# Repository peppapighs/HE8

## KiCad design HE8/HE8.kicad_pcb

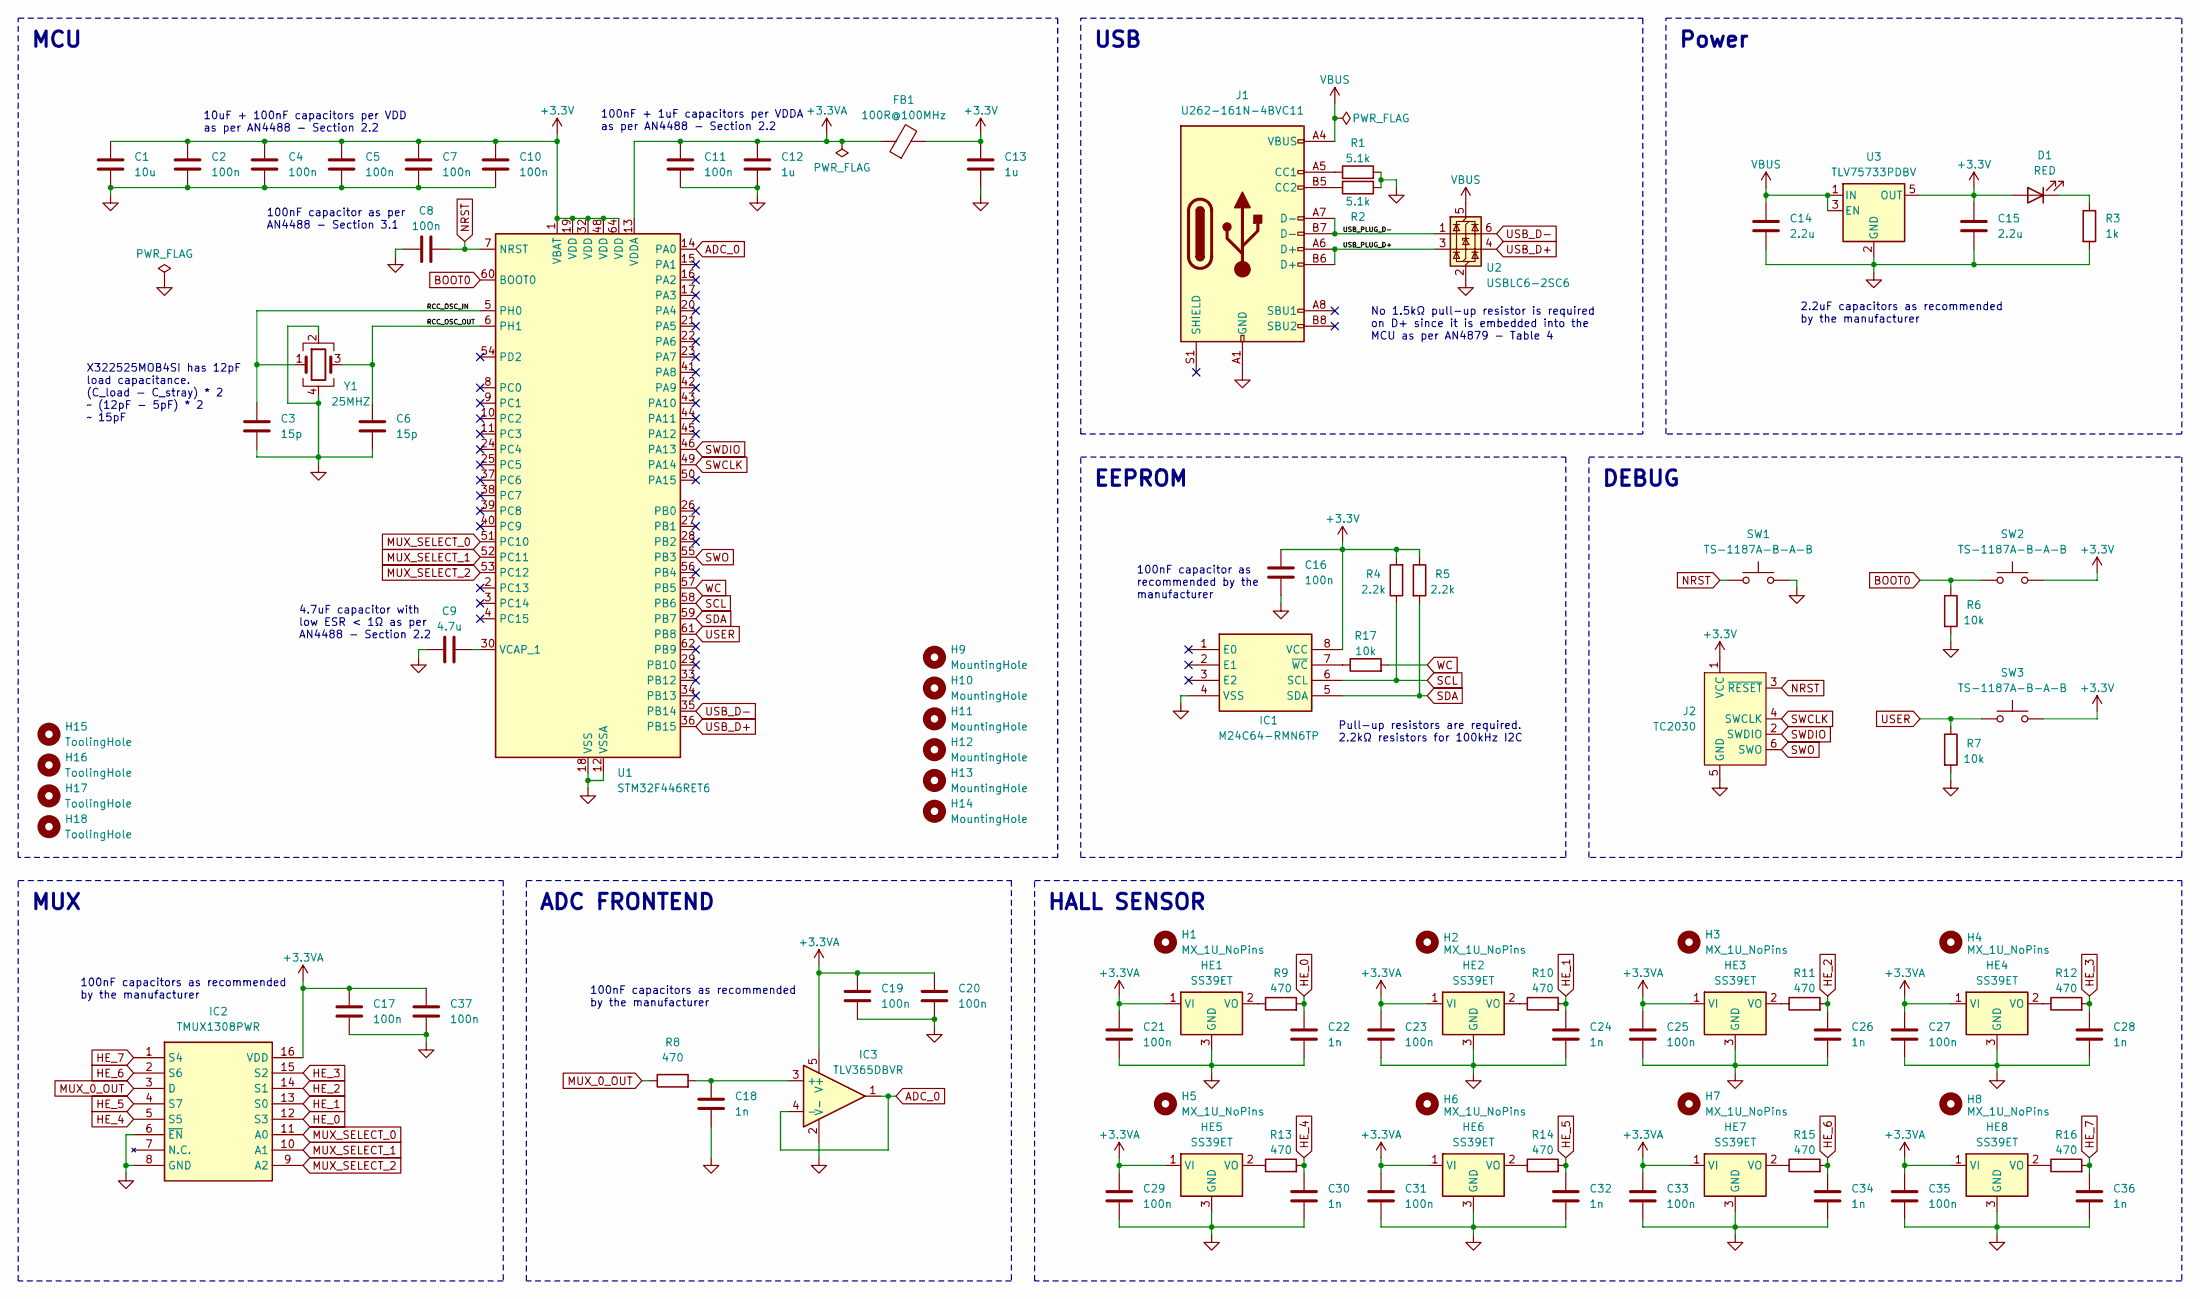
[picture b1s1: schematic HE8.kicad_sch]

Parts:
C1: 10u; C_0603_1608Metric
C2, C4, C5, C7, C8, C10, C11, C16, C17, C19, C20, C21, C23, C25, C27, C29, C31, C33, C35, C37: 100n; C_0402_1005Metric
C3, C6: 15p; C_0402_1005Metric
C9: 4.7u; C_0603_1608Metric
C12, C13: 1u; C_0603_1608Metric
C14, C15: 2.2u; C_0603_1608Metric
C18, C22, C24, C26, C28, C30, C32, C34, C36: 1n; C_0402_1005Metric
D1: RED; LED_0402_1005Metric
FB1: 100R@100MHz; L_0805_2012Metric
H1, H2, H3, H4, H5, H6, H7, H8: MX_1U_NoPins; MX-1U-NoPins
H9, H10, H11, H12, H13, H14: MountingHole; MountingHole_3.2mm_M3
H15, H16, H17, H18: ToolingHole
HE1, HE2, HE3, HE4, HE5, HE6, HE7, HE8: SS39ET; SOT95P280X140-3N; Mouser Part Number 785-SS39ET
IC1: M24C64-RMN6TP; SOIC127P600X175-8N; Mouser Part Number 511-M24C64-RMN6TP
IC2: TMUX1308PWR; SOP65P640X120-16N; Manufacturer_Part_Number TMUX1308PWR; Mouser Part Number 595-TMUX1308PWR
IC3: TLV365DBVR; SOT95P280X145-5N; Manufacturer_Part_Number TLV365DBVR
J1: U262-161N-4BVC11; USB_C_Receptacle_XKB_U262-16XN-4BVC11
J2: TC2030; Tag-Connect_TC2030-IDC-FP_2x03_P1.27mm_Vertical
R1, R2: 5.1k; R_0402_1005Metric
R3: 1k; R_0402_1005Metric
R4, R5: 2.2k; R_0402_1005Metric
R6, R7, R17: 10k; R_0402_1005Metric
R8, R9, R10, R11, R12, R13, R14, R15, R16: 470; R_0402_1005Metric
SW1, SW2, SW3: TS-1187A-B-A-B; SW_Push_1P1T_XKB_TS-1187A
U1: STM32F446RET6; LQFP-64_10x10mm_P0.5mm
U2: USBLC6-2SC6; SOT-23-6
U3: TLV75733PDBV; SOT-23-5
Y1: 25MHZ; Crystal_SMD_3225-4Pin_3.2x2.5mm

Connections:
+3.3V: C1.1, C2.1, C4.1, C5.1, C7.1, C10.1, C13.1, C15.1, C16.1, D1.2 (A), FB1.2, IC1.8 (VCC), J2.1 (VCC), R4.2, R5.1, SW2.2, SW3.2, U1.1 (VBAT), U1.19 (VDD), U1.32 (VDD), U1.48 (VDD), U1.64 (VDD), U3.5 (OUT)
+3.3VA: C11.1, C12.1, C17.1, C19.1, C20.1, C21.1, C23.1, C25.1, C27.1, C29.1, C31.1, C33.1, C35.1, C37.1, FB1.1, HE1.1 (VI), HE2.1 (VI), HE3.1 (VI), HE4.1 (VI), HE5.1 (VI), HE6.1 (VI), HE7.1 (VI), HE8.1 (VI), IC2.16 (VDD), IC3.5 (V+), U1.13 (VDDA)
/RCC_OSC_IN: C3.1, U1.5 (PH0), Y1.1
/RCC_OSC_OUT: C6.1, U1.6 (PH1), Y1.3
/USB_PLUG_D+: J1.A6 (D+), J1.B6 (D+), U2.3 (I/O2)
/USB_PLUG_D-: J1.A7 (D-), J1.B7 (D-), U2.1 (I/O1)
ADC_0: IC3.1, IC3.4 (-), U1.14 (PA0)
BOOT0: R6.1, SW2.1, U1.60 (BOOT0)
GND: C1.2, C2.2, C3.2, C4.2, C5.2, C6.2, C7.2, C8.1, C9.1, C10.2, C11.2, C12.2, C13.2, C14.2, C15.2, C16.2, C17.2, C18.2, C19.2, C20.2, C21.2, C22.2, C23.2, C24.2, C25.2, C26.2, C27.2, C28.2, C29.2, C30.2, C31.2, C32.2, C33.2, C34.2, C35.2, C36.2, C37.2, HE1.3 (GND), HE2.3 (GND), HE3.3 (GND), HE4.3 (GND), HE5.3 (GND), HE6.3 (GND), HE7.3 (GND), HE8.3 (GND), IC1.4 (VSS), IC2.6 (~EN), IC2.8 (GND), IC3.2 (V-), J1.A1 (GND), J1.A12 (GND), J1.B1 (GND), J1.B12 (GND), J2.5 (GND), R1.2, R2.1, R3.2, R6.2, R7.2, SW1.2, U1.12 (VSSA), U1.18 (VSS), U1.31 (VSS), U1.47 (VSS), U1.63 (VSS), U2.2 (GND), U3.2 (GND), Y1.2, Y1.4
HE_0: C22.1, IC2.12 (S3), R9.2
HE_1: C24.1, IC2.13 (S0), R10.2
HE_2: C26.1, IC2.14 (S1), R11.2
HE_3: C28.1, IC2.15 (S2), R12.2
HE_4: C30.1, IC2.5 (S5), R13.2
HE_5: C32.1, IC2.4 (S7), R14.2
HE_6: C34.1, IC2.2 (S6), R15.2
HE_7: C36.1, IC2.1 (S4), R16.2
MUX_0_OUT: IC2.3 (D), R8.1
MUX_SELECT_0: IC2.11 (A0), U1.51 (PC10)
MUX_SELECT_1: IC2.10 (A1), U1.52 (PC11)
MUX_SELECT_2: IC2.9 (A2), U1.53 (PC12)
NRST: C8.2, J2.3 (~RESET), SW1.1, U1.7 (NRST)
unnamed: D1.1 (K), R3.1
unnamed: HE1.2 (VO), R9.1
unnamed: HE2.2 (VO), R10.1
unnamed: HE3.2 (VO), R11.1
unnamed: HE4.2 (VO), R12.1
unnamed: HE5.2 (VO), R13.1
unnamed: HE6.2 (VO), R14.1
unnamed: HE7.2 (VO), R15.1
unnamed: HE8.2 (VO), R16.1
unnamed: IC1.7 (~WC), R17.1
unnamed: C18.1, IC3.3 (+), R8.2
unnamed: J1.A5 (CC1), R1.1
unnamed: J1.B5 (CC2), R2.2
unnamed: C9.2, U1.30 (VCAP_1)
SCL: IC1.6 (SCL), R4.1, U1.58 (PB6)
SDA: IC1.5 (SDA), R5.2, U1.59 (PB7)
SWCLK: J2.4 (SWCLK), U1.49 (PA14)
SWDIO: J2.2 (SWDIO), U1.46 (PA13)
SWO: J2.6 (SWO), U1.55 (PB3)
USB_D+: U1.36 (PB15), U2.4 (I/O2)
USB_D-: U1.35 (PB14), U2.6 (I/O1)
USER: R7.1, SW3.1, U1.61 (PB8)
VBUS: C14.1, J1.A4 (VBUS), J1.A9 (VBUS), J1.B4 (VBUS), J1.B9 (VBUS), U2.5 (VBUS), U3.1 (IN), U3.3 (EN)
WC: R17.2, U1.57 (PB5)

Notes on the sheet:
USB
MCU
ADC FRONTEND
EEPROM
DEBUG
HALL SENSOR
Power
MUX
X322525MOB4SI has 12pF load capacitance. (C_load - C_stray) * 2 ~ (12pF - 5pF) * 2 ~ 15pF
100nF capacitor as per AN4488 - Section 3.1
4.7uF capacitor with low ESR < 1Ω as per AN4488 - Section 2.2
100nF + 1uF capacitors per VDDA as per AN4488 - Section 2.2
2.2uF capacitors as recommended by the manufacturer
100nF capacitors as recommended by the manufacturer
No 1.5kΩ pull-up resistor is required on D+ since it is embedded into the MCU as per AN4879 - Table 4
10uF + 100nF capacitors per VDD as per AN4488 - Section 2.2
Pull-up resistors are required. 2.2kΩ resistors for 100kHz I2C
100nF capacitor as recommended by the manufacturer

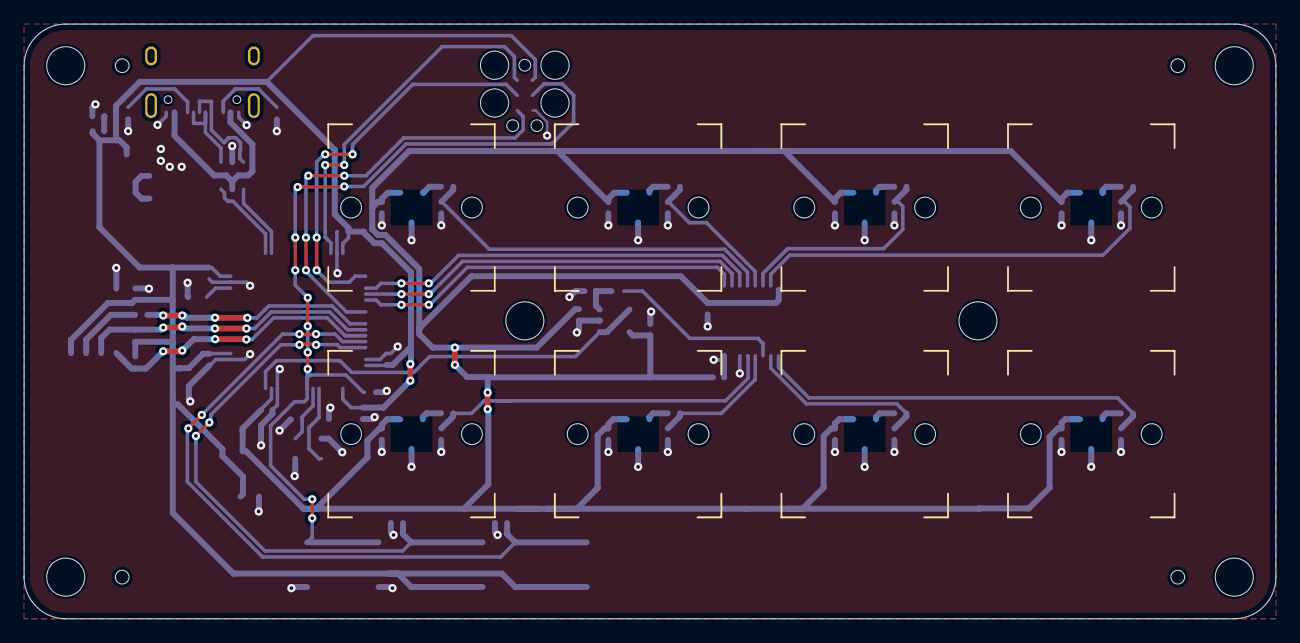
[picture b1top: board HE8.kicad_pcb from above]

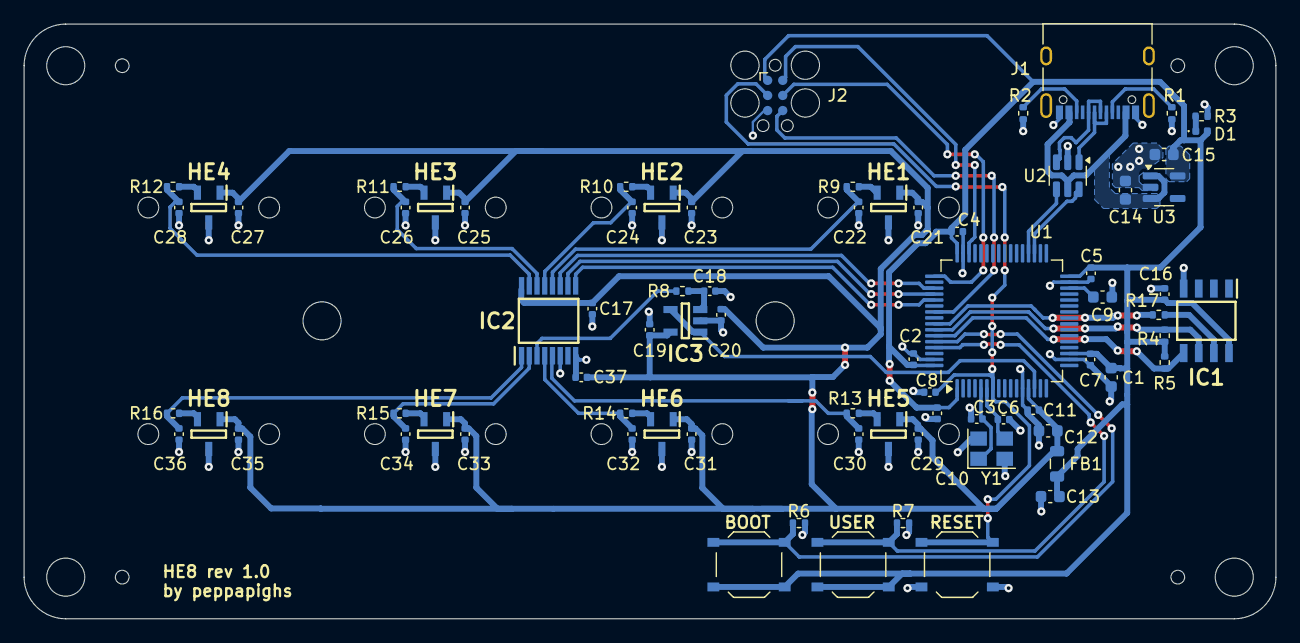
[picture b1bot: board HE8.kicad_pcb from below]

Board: 2 copper layers, 105.3 x 50.0 mm, 94 parts (82 on the bottom side), 46 nets.

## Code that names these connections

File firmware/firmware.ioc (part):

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Mcu.Name=STM32F446R(C-E)Tx
Mcu.Package=LQFP64
Mcu.UserName=STM32F446RETx
PA0-WKUP.Signal=ADCx_IN0
PA13.Mode=Trace_Asynchronous_SW
PA13.Signal=SYS_JTMS-SWDIO
PA14.Mode=Trace_Asynchronous_SW
PA14.Signal=SYS_JTCK-SWCLK
PB14.Mode=Device_Only_FS
PB14.Signal=USB_OTG_HS_DM
PB15.Mode=Device_Only_FS
PB15.Signal=USB_OTG_HS_DP
PB3.Mode=Trace_Asynchronous_SW
PB3.Signal=SYS_JTDO-SWO
PB5.GPIOParameters=GPIO_Speed,GPIO_Label
PB5.GPIO_Label=WC
PB5.GPIO_Speed=GPIO_SPEED_FREQ_HIGH
PB5.Signal=GPIO_Output
PB6.Mode=I2C
PB6.Signal=I2C1_SCL
PB7.Mode=I2C
PB7.Signal=I2C1_SDA
PB8.GPIOParameters=GPIO_Label
PB8.GPIO_Label=USER
PB8.Signal=GPIO_Input
PC10.GPIOParameters=GPIO_Speed,GPIO_Label
PC10.GPIO_Label=MUX_SELECT_0
PC10.GPIO_Speed=GPIO_SPEED_FREQ_VERY_HIGH
PC10.Signal=GPIO_Output
PC11.GPIOParameters=GPIO_Speed,GPIO_Label
PC11.GPIO_Label=MUX_SELECT_1
PC11.GPIO_Speed=GPIO_SPEED_FREQ_VERY_HIGH
PC11.Signal=GPIO_Output
PC12.GPIOParameters=GPIO_Speed,GPIO_Label
PC12.GPIO_Label=MUX_SELECT_2
PC12.GPIO_Speed=GPIO_SPEED_FREQ_VERY_HIGH
PC12.Signal=GPIO_Output
PH0-OSC_IN.Mode=HSE-External-Oscillator
PH0-OSC_IN.Signal=RCC_OSC_IN
PH1-OSC_OUT.Mode=HSE-External-Oscillator
PH1-OSC_OUT.Signal=RCC_OSC_OUT
RCC.SYSCLKFreq_VALUE=180000000
RCC.SYSCLKSource=RCC_SYSCLKSOURCE_PLLCLK
board=custom

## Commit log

2024-11-04 add plate arts
2024-11-05 add bootloader
2024-11-05 add skeleton code for firmware
2024-11-06 add basic rapid trigger firmware
2024-11-06 add firmware checksum padding script & fix bootloader crc bug
2024-11-06 fix integer overflow causing irratic adc readings
2024-11-07 add keyboard config struct
2024-11-10 digitally filter noise using exponential smoothing
2024-11-11 use quadratic interpolation for more accurate switch distance
2024-11-12 add consumer and system control keycodes
2024-11-12 fix keyboard not sending keycodes bug
2024-11-12 refactor hid related code
2024-11-12 use hard-coded HID keycodes instead of tinyusb macros
2024-11-12 implement layer keys
2024-11-13 fix one shot keys algorithm
2024-11-13 implement modifier keys & remote wakeup
2024-11-13 add extra consumer keycodes
2024-11-13 enable O2 optimization for release build
2024-11-13 save config to eeprom & add profile switching
2024-11-13 refactor code & add switch profile switching
2024-11-14 fix one-time key bug
2024-11-14 add tap-hold behavior and latency debugging
2024-11-14 optimize polling latency
2024-11-14 change transparent key behavior and refactor
2024-11-14 optimize key switch polling
2024-11-15 refactor firmware code
2024-11-15 add variable to adjust the aggressiveness of the quadratic curve
2024-11-16 add section comments
2024-11-16 replace duplicates with aliases instead in keycodes
2024-11-16 test some vendor class protocols
2024-11-17 precompute the distance conversion table
2024-11-17 add more vendor class protocols
2024-11-18 add enum values for key switch state
2024-11-18 add LICENSE
2024-11-18 implement eeprom & vendor protocols
2024-11-19 add vendor protocol for firmware version request
2024-11-19 add NKRO support
2024-11-19 add vendor protocols for recalibrate & NKRO toggling
2024-11-19 add firmware related keycodes
2024-11-22 add rounding to the distance calculation
2024-11-28 enable release build
